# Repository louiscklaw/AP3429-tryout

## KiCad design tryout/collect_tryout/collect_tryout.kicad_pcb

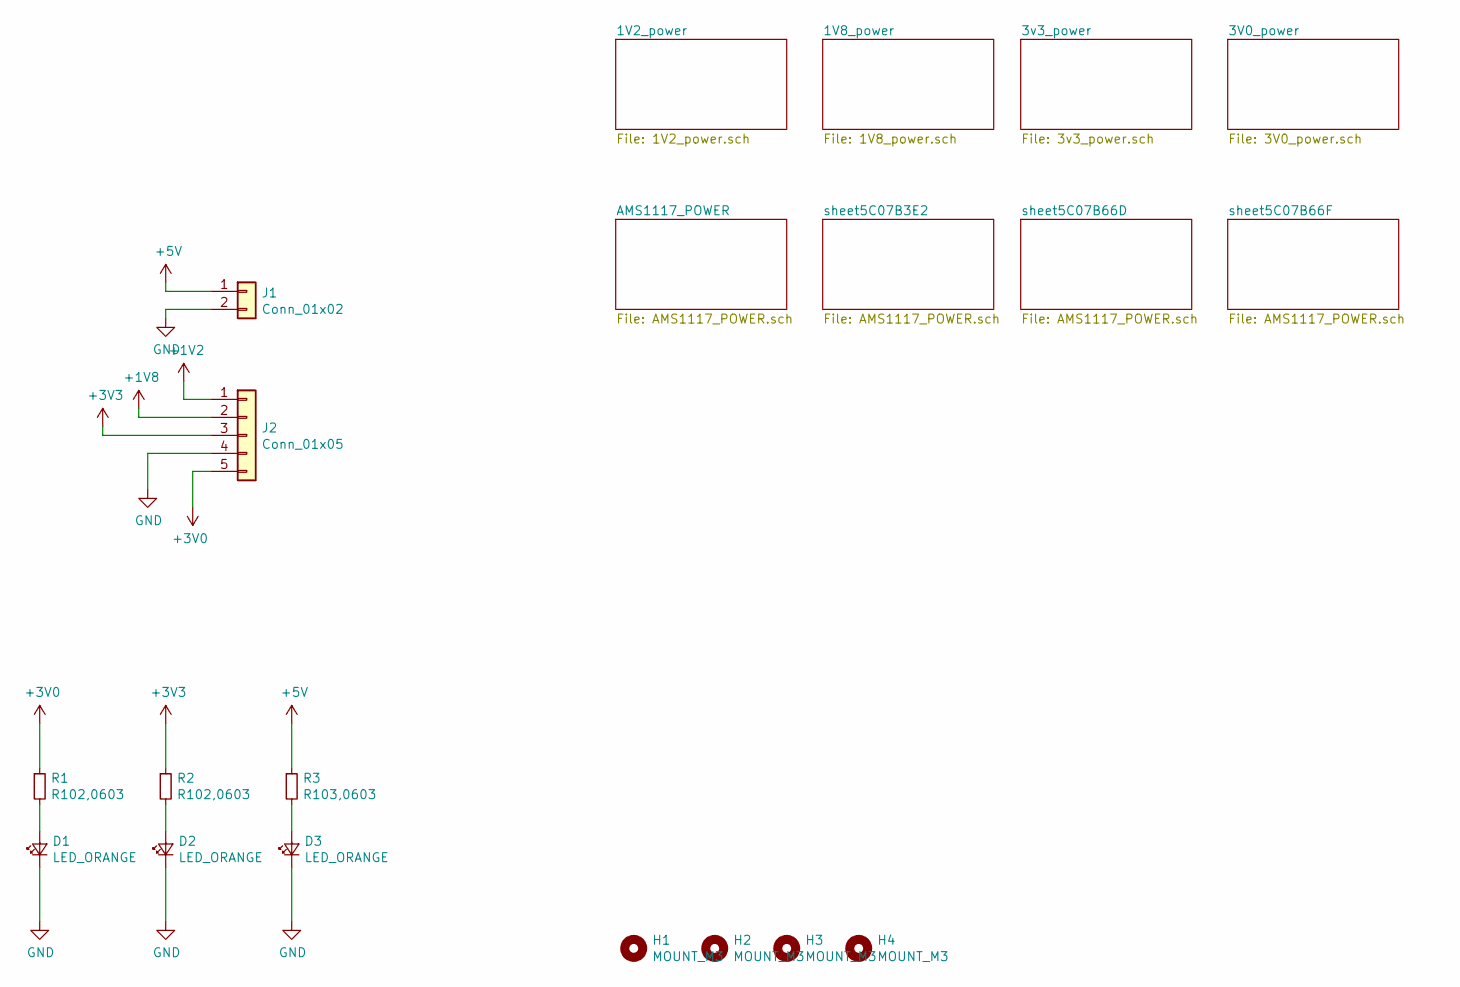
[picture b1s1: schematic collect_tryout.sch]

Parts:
D1, D2, D3: LED_ORANGE; LED_0805_2012Metric_Castellated
H1, H2, H3, H4: MOUNT_M3; MountingHole_3.2mm_M3_DIN965
J1: Conn_01x02; PinHeader_1x02_P2.54mm_Vertical
J2: Conn_01x05; PinHeader_1x05_P2.54mm_Vertical
R1, R2: R102,0603; R_0603_1608Metric_Pad1.05x0.95mm_HandSolder
R3: R103,0603; R_0603_1608Metric_Pad1.05x0.95mm_HandSolder

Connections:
+1V2: J2.1; also elsewhere on the board
+1V8: J2.2; also elsewhere on the board
+3V0: J2.5, R1.1; also elsewhere on the board
+3V3: J2.3, R2.1; also elsewhere on the board
+5V: J1.1, R3.1; also elsewhere on the board
GND: D1.1 (K), D2.1 (K), D3.1 (K), J1.2, J2.4; also elsewhere on the board
unnamed: D1.2 (A), R1.2
unnamed: D2.2 (A), R2.2
unnamed: D3.2 (A), R3.2

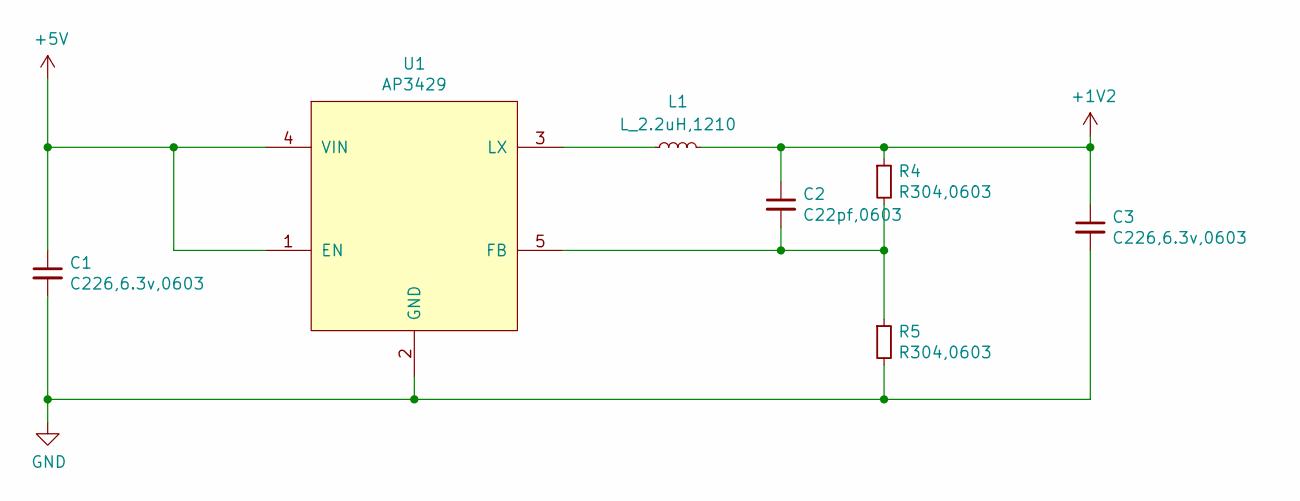
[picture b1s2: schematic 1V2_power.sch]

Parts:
C1, C3: C226,6.3v,0603; C_0603_1608Metric_Pad1.05x0.95mm_HandSolder
C2: C22pf,0603; C_0603_1608Metric_Pad1.05x0.95mm_HandSolder
L1: L_2.2uH,1210; L_1210_3225Metric_Pad1.42x2.65mm_HandSolder
R4, R5: R304,0603; R_0603_1608Metric_Pad1.05x0.95mm_HandSolder
U1: AP3429; TSOT-23-5

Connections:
+1V2: C2.1, C3.1, L1.2, R4.1; also elsewhere on the board
+5V: C1.1, U1.1 (EN), U1.4 (VIN); also elsewhere on the board
GND: C1.2, C3.2, R5.2, U1.2 (GND); also elsewhere on the board
unnamed: C2.2, R4.2, R5.1, U1.5 (FB)
unnamed: L1.1, U1.3 (LX)

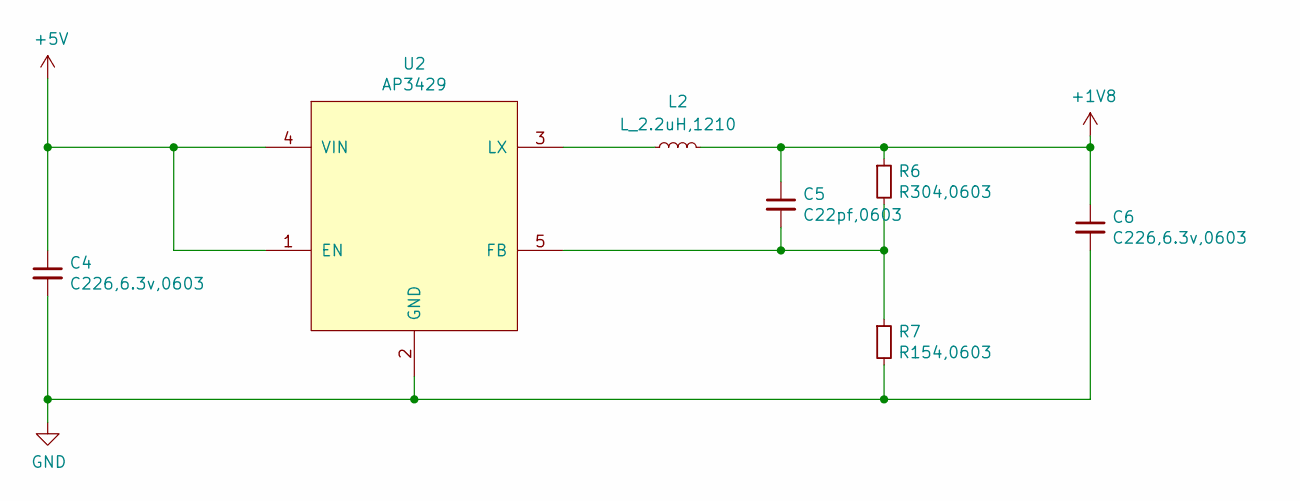
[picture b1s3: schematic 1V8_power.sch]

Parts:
C4, C6: C226,6.3v,0603; C_0603_1608Metric_Pad1.05x0.95mm_HandSolder
C5: C22pf,0603; C_0603_1608Metric_Pad1.05x0.95mm_HandSolder
L2: L_2.2uH,1210; L_1210_3225Metric_Pad1.42x2.65mm_HandSolder
R6: R304,0603; R_0603_1608Metric_Pad1.05x0.95mm_HandSolder
R7: R154,0603; R_0603_1608Metric_Pad1.05x0.95mm_HandSolder
U2: AP3429; TSOT-23-5

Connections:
+1V8: C5.1, C6.1, L2.2, R6.1; also elsewhere on the board
+5V: C4.1, U2.1 (EN), U2.4 (VIN); also elsewhere on the board
GND: C4.2, C6.2, R7.2, U2.2 (GND); also elsewhere on the board
unnamed: C5.2, R6.2, R7.1, U2.5 (FB)
unnamed: L2.1, U2.3 (LX)

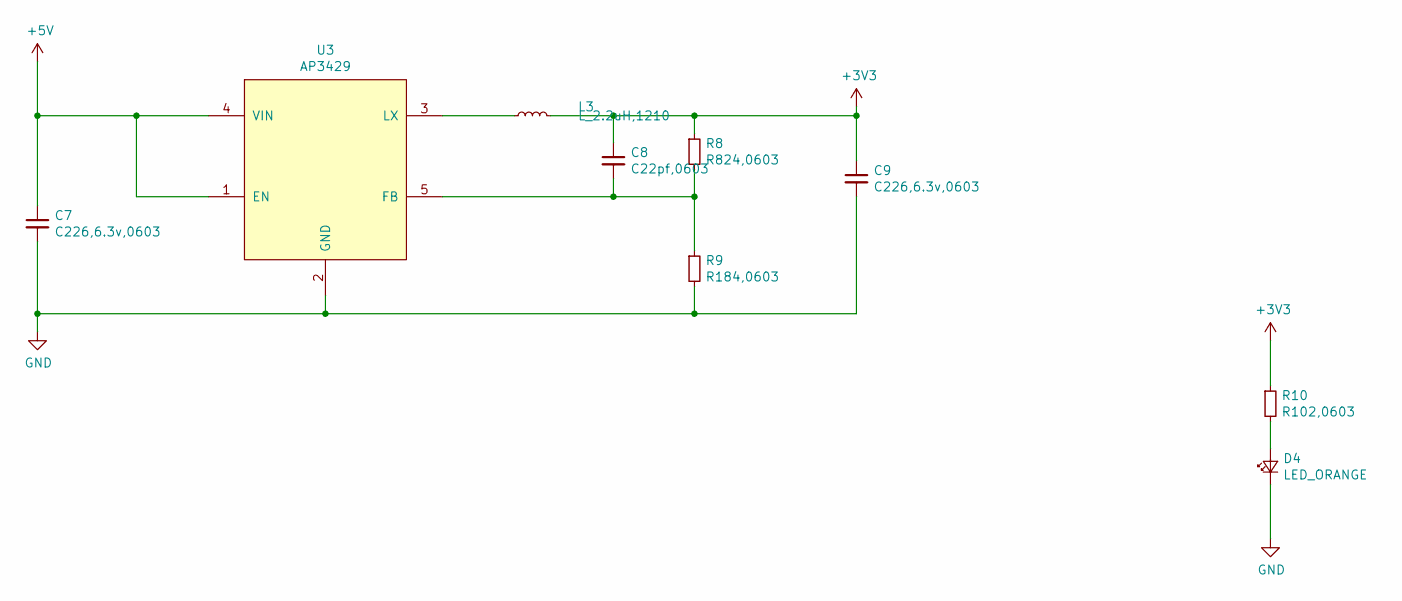
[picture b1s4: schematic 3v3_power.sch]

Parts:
C7, C9: C226,6.3v,0603; C_0603_1608Metric_Pad1.05x0.95mm_HandSolder
C8: C22pf,0603; C_0603_1608Metric_Pad1.05x0.95mm_HandSolder
D4: LED_ORANGE; LED_0805_2012Metric_Castellated
L3: L_2.2uH,1210; L_1210_3225Metric_Pad1.42x2.65mm_HandSolder
R8: R824,0603; R_0603_1608Metric_Pad1.05x0.95mm_HandSolder
R9: R184,0603; R_0603_1608Metric_Pad1.05x0.95mm_HandSolder
R10: R102,0603; R_0603_1608Metric_Pad1.05x0.95mm_HandSolder
U3: AP3429; TSOT-23-5

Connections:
+3V3: C8.1, C9.1, L3.2, R8.1, R10.1; also elsewhere on the board
+5V: C7.1, U3.1 (EN), U3.4 (VIN); also elsewhere on the board
GND: C7.2, C9.2, D4.1 (K), R9.2, U3.2 (GND); also elsewhere on the board
unnamed: C8.2, R8.2, R9.1, U3.5 (FB)
unnamed: D4.2 (A), R10.2
unnamed: L3.1, U3.3 (LX)

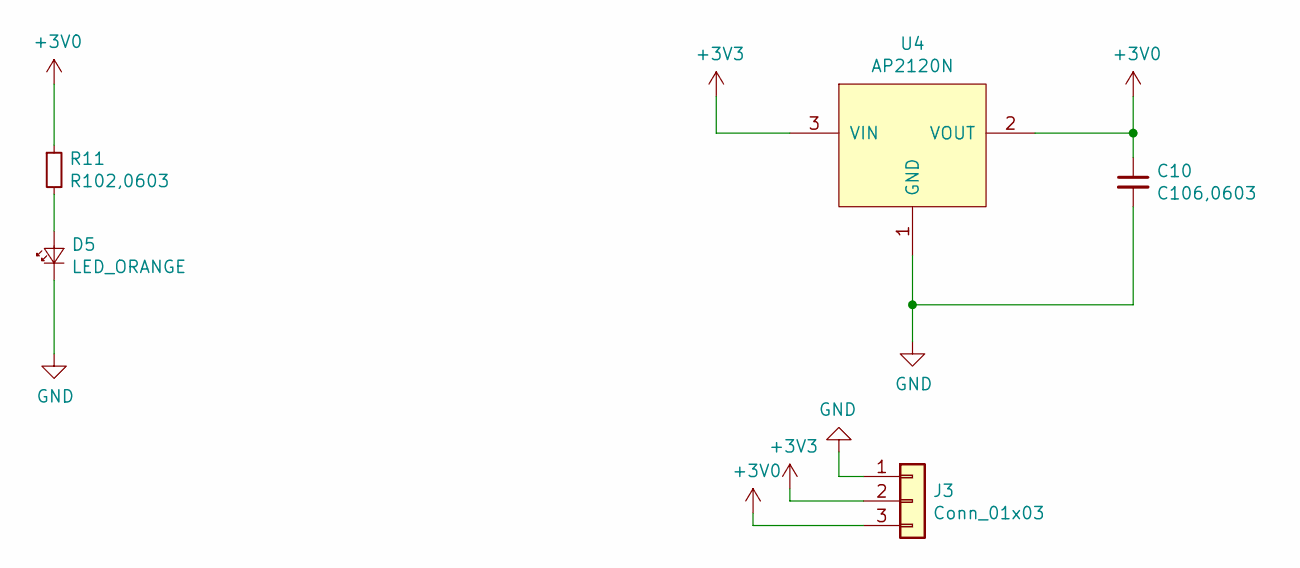
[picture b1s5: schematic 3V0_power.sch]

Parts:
C10: C106,0603; C_0603_1608Metric_Pad1.05x0.95mm_HandSolder
D5: LED_ORANGE; LED_0805_2012Metric_Castellated
J3: Conn_01x03; PinHeader_1x03_P2.54mm_Vertical
R11: R102,0603; R_0603_1608Metric_Pad1.05x0.95mm_HandSolder
U4: AP2120N; SOT-23_Handsoldering

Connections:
+3V0: C10.1, J3.3, R11.1, U4.2 (VOUT); also elsewhere on the board
+3V3: J3.2, U4.3 (VIN); also elsewhere on the board
GND: C10.2, D5.1 (K), J3.1, U4.1 (GND); also elsewhere on the board
unnamed: D5.2 (A), R11.2

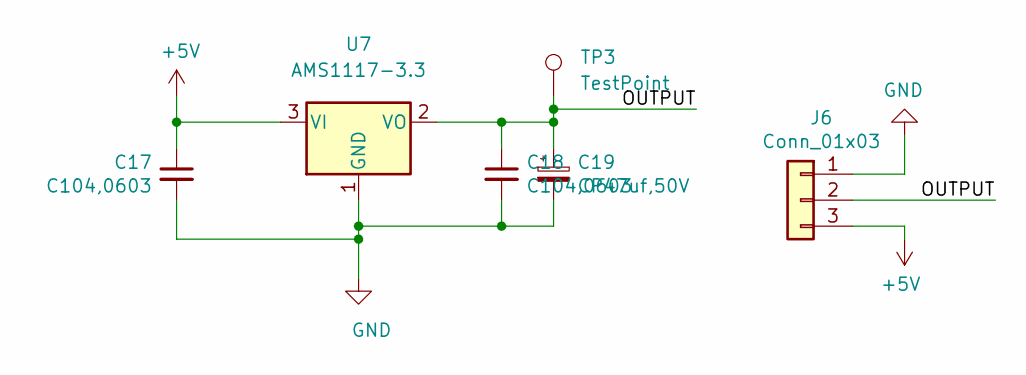
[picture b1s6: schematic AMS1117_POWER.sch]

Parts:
C11, C12: C104,0603; C_0603_1608Metric_Pad1.05x0.95mm_HandSolder
C13: CP47uf,50V; c_elec_6.3x7.7
J4: Conn_01x03; PinHeader_1x03_P2.54mm_Vertical
TP1: TestPoint; TestPoint_Keystone_5019_Minature
U5: AMS1117-3.3; SOT-223-3_TabPin2

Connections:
+5V: C11.1, J4.3, U5.3 (VI); also elsewhere on the board
/AMS1117_POWER/OUTPUT: C12.1, C13.1, J4.2, TP1.1, U5.2 (VO)
GND: C11.2, C12.2, C13.2, J4.1, U5.1 (GND); also elsewhere on the board

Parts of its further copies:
C14, C15, C17, C18, C20, C21: C104,0603; C_0603_1608Metric_Pad1.05x0.95mm_HandSolder
C16, C19, C22: CP47uf,50V; c_elec_6.3x7.7
J5, J6, J7: Conn_01x03; PinHeader_1x03_P2.54mm_Vertical
TP2, TP3, TP4: TestPoint; TestPoint_Keystone_5019_Minature
U6, U7, U8: AMS1117-3.3; SOT-223-3_TabPin2

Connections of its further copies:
+5V: C14.1, C17.1, C20.1, J5.3, J6.3, J7.3, U6.3 (VI), U7.3 (VI), U8.3 (VI); also elsewhere on the board
/sheet5C07B3E2/OUTPUT: C15.1, C16.1, J5.2, TP2.1, U6.2 (VO)
/sheet5C07B66D/OUTPUT: C18.1, C19.1, J6.2, TP3.1, U7.2 (VO)
/sheet5C07B66F/OUTPUT: C21.1, C22.1, J7.2, TP4.1, U8.2 (VO)
GND: C14.2, C15.2, C16.2, C17.2, C18.2, C19.2, C20.2, C21.2, C22.2, J5.1, J6.1, J7.1, U6.1 (GND), U7.1 (GND), U8.1 (GND); also elsewhere on the board

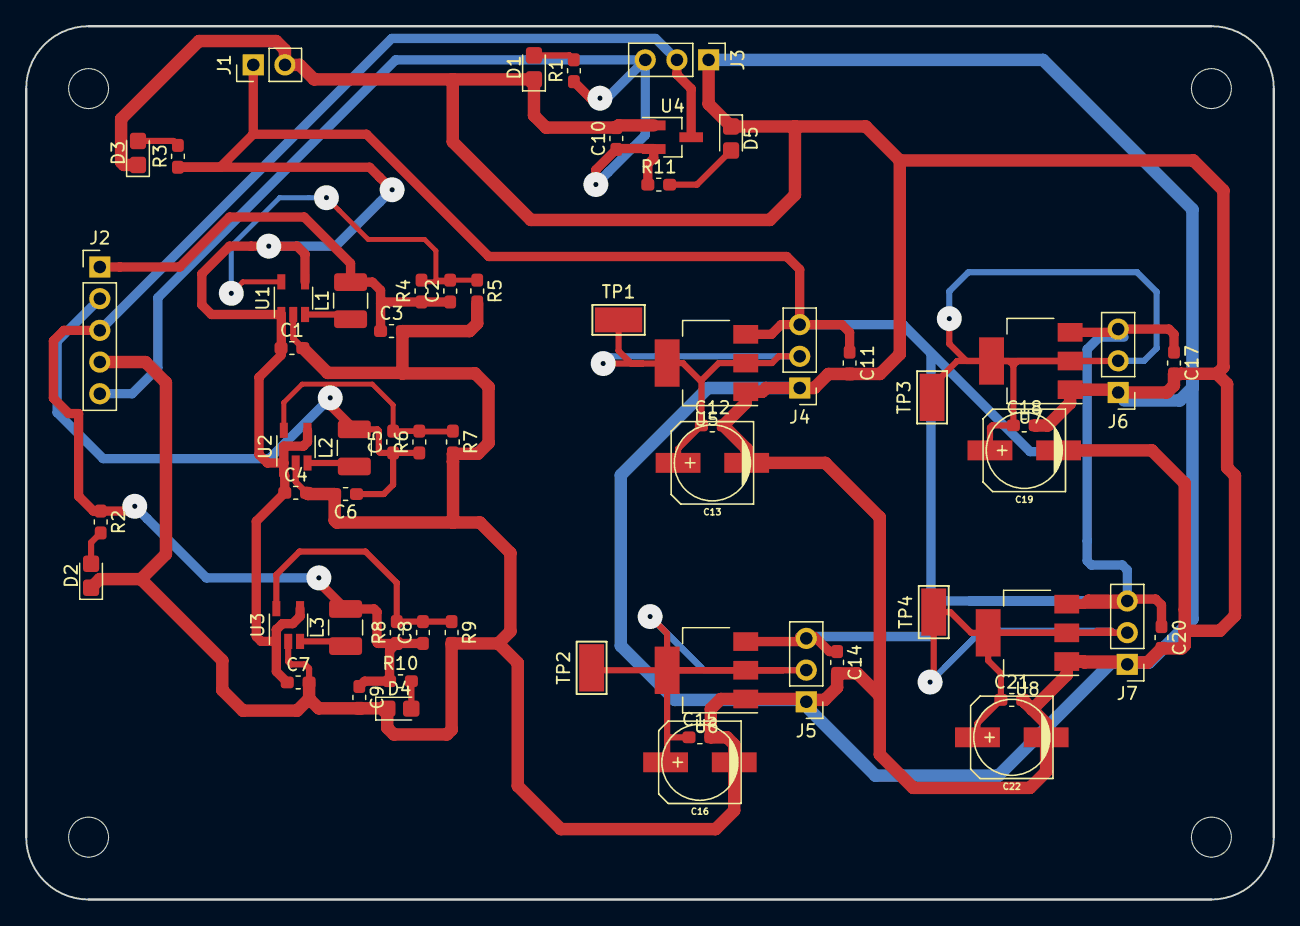
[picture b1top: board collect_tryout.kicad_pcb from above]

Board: 2 copper layers, 100.0 x 70.0 mm, 64 parts (0 on the bottom side), 21 nets.

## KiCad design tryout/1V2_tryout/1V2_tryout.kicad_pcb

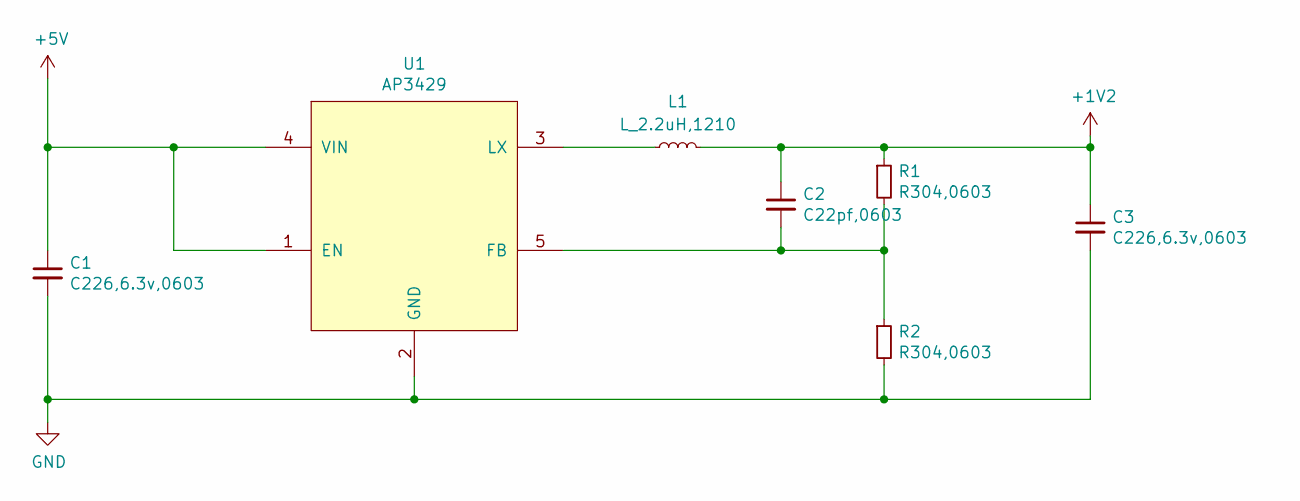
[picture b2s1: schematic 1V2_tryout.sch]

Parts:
C1, C3: C226,6.3v,0603; C_0603_1608Metric_Pad1.05x0.95mm_HandSolder
C2: C22pf,0603; C_0603_1608Metric_Pad1.05x0.95mm_HandSolder
L1: L_2.2uH,1210; L_1210_3225Metric_Pad1.42x2.65mm_HandSolder
R1, R2: R304,0603; R_0603_1608Metric_Pad1.05x0.95mm_HandSolder
U1: AP3429; TSOT-23-5

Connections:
+1V2: C2.1, C3.1, L1.2, R1.1
+5V: C1.1, U1.1 (EN), U1.4 (VIN)
GND: C1.2, C3.2, R2.2, U1.2 (GND)
unnamed: C2.2, R1.2, R2.1, U1.5 (FB)
unnamed: L1.1, U1.3 (LX)

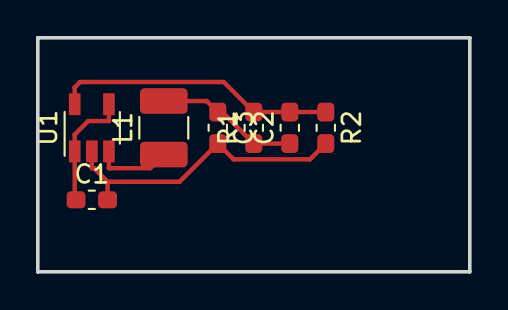
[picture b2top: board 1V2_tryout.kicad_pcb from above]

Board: 2 copper layers, 24.0 x 13.0 mm, 7 parts (0 on the bottom side), 5 nets.

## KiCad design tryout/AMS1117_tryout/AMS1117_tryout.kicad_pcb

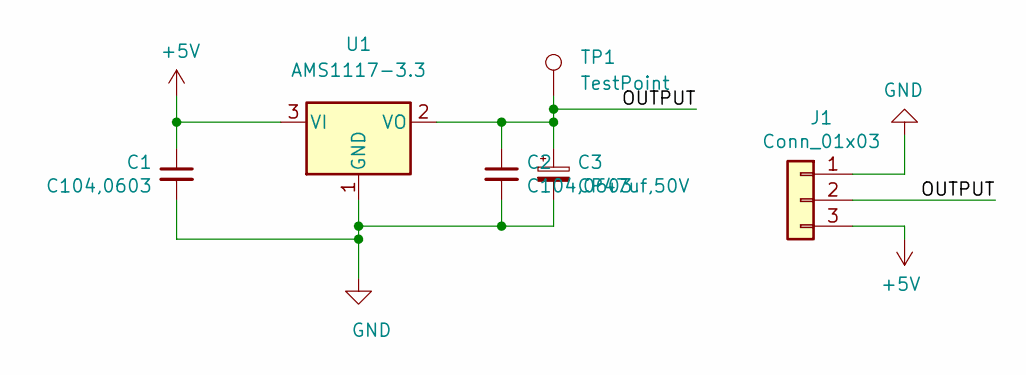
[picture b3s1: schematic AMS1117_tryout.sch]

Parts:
C1, C2: C104,0603; C_0603_1608Metric_Pad1.05x0.95mm_HandSolder
C3: CP47uf,50V; c_elec_6.3x7.7
J1: Conn_01x03; PinHeader_1x03_P2.54mm_Vertical
TP1: TestPoint; TestPoint_Keystone_5019_Minature
U1: AMS1117-3.3; SOT-223-3_TabPin2

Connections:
+5V: C1.1, J1.3, U1.3 (VI)
/OUTPUT: C2.1, C3.1, J1.2, TP1.1, U1.2 (VO)
GND: C1.2, C2.2, C3.2, J1.1, U1.1 (GND)

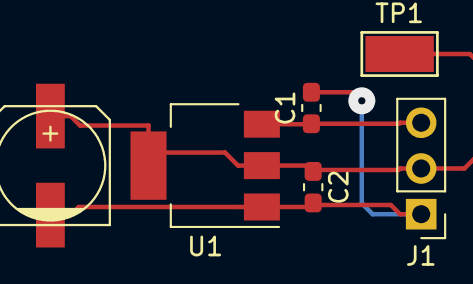
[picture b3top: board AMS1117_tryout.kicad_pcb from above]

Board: 2 copper layers, 6 parts (0 on the bottom side), 3 nets.

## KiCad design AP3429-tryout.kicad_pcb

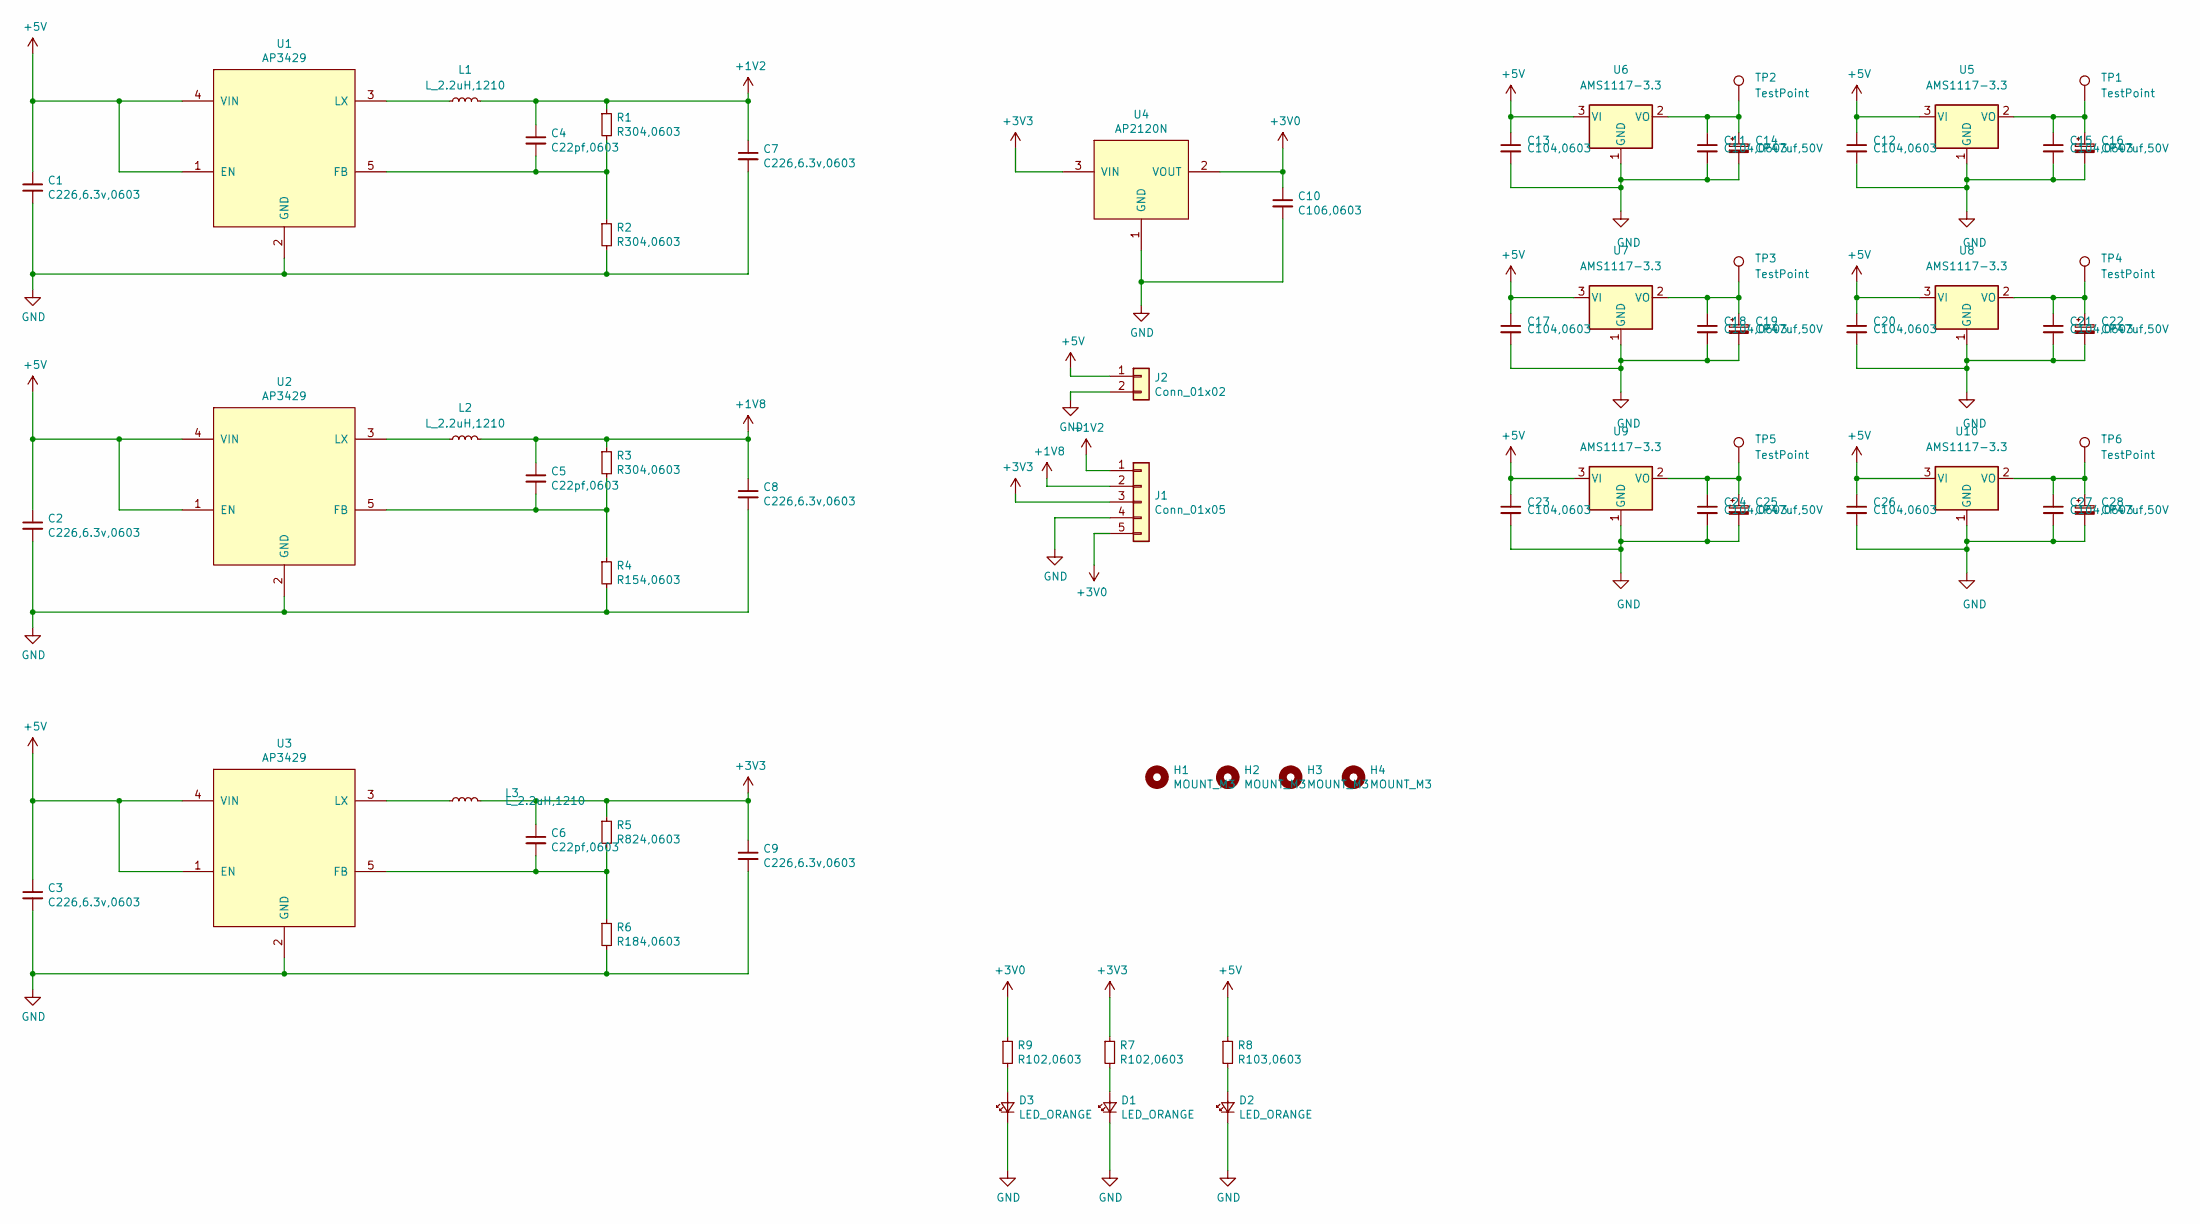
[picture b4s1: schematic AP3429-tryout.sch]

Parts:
C1, C2, C3, C7, C8, C9: C226,6.3v,0603; C_0603_1608Metric_Pad1.05x0.95mm_HandSolder
C4, C5, C6: C22pf,0603; C_0603_1608Metric_Pad1.05x0.95mm_HandSolder
C10: C106,0603; C_0603_1608Metric_Pad1.05x0.95mm_HandSolder
C11, C12, C13, C15, C17, C18, C20, C21, C23, C24, C26, C27: C104,0603; C_0603_1608Metric_Pad1.05x0.95mm_HandSolder
C14, C16, C19, C22, C25, C28: CP47uf,50V; c_elec_6.3x7.7
D1, D2, D3: LED_ORANGE; LED_0805_2012Metric_Castellated
H1, H2, H3, H4: MOUNT_M3; MountingHole_3.2mm_M3_DIN965
J1: Conn_01x05; PinHeader_1x05_P2.54mm_Vertical
J2: Conn_01x02; PinHeader_1x02_P2.54mm_Vertical
L1, L2, L3: L_2.2uH,1210; L_1210_3225Metric_Pad1.42x2.65mm_HandSolder
R1, R2, R3: R304,0603; R_0603_1608Metric_Pad1.05x0.95mm_HandSolder
R4: R154,0603; R_0603_1608Metric_Pad1.05x0.95mm_HandSolder
R5: R824,0603; R_0603_1608Metric_Pad1.05x0.95mm_HandSolder
R6: R184,0603; R_0603_1608Metric_Pad1.05x0.95mm_HandSolder
R7, R9: R102,0603; R_0603_1608Metric_Pad1.05x0.95mm_HandSolder
R8: R103,0603; R_0603_1608Metric_Pad1.05x0.95mm_HandSolder
TP1, TP2, TP3, TP4, TP5, TP6: TestPoint; TestPoint_Keystone_5019_Minature
U1, U2, U3: AP3429; TSOT-23-5
U4: AP2120N; SOT-23_Handsoldering
U5, U6, U7, U8, U9, U10: AMS1117-3.3; SOT-223-3_TabPin2

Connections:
+1V2: C4.1, C7.1, J1.1, L1.2, R1.1
+1V8: C5.1, C8.1, J1.2, L2.2, R3.1
+3V0: C10.1, J1.5, R9.1, U4.2 (VOUT)
+3V3: C6.1, C9.1, J1.3, L3.2, R5.1, R7.1, U4.3 (VIN)
+5V: C1.1, C2.1, C3.1, C12.1, C13.1, C17.1, C20.1, C23.1, C26.1, J2.1, R8.1, U1.1 (EN), U1.4 (VIN), U2.1 (EN), U2.4 (VIN), U3.1 (EN), U3.4 (VIN), U5.3 (VI), U6.3 (VI), U7.3 (VI), U8.3 (VI), U9.3 (VI), U10.3 (VI)
GND: C1.2, C2.2, C3.2, C7.2, C8.2, C9.2, C10.2, C11.2, C12.2, C13.2, C14.2, C15.2, C16.2, C17.2, C18.2, C19.2, C20.2, C21.2, C22.2, C23.2, C24.2, C25.2, C26.2, C27.2, C28.2, D1.1 (K), D2.1 (K), D3.1 (K), J1.4, J2.2, R2.2, R4.2, R6.2, U1.2 (GND), U2.2 (GND), U3.2 (GND), U4.1 (GND), U5.1 (GND), U6.1 (GND), U7.1 (GND), U8.1 (GND), U9.1 (GND), U10.1 (GND)
unnamed: C4.2, R1.2, R2.1, U1.5 (FB)
unnamed: C5.2, R3.2, R4.1, U2.5 (FB)
unnamed: C6.2, R5.2, R6.1, U3.5 (FB)
unnamed: C11.1, C14.1, TP2.1, U6.2 (VO)
unnamed: C15.1, C16.1, TP1.1, U5.2 (VO)
unnamed: C18.1, C19.1, TP3.1, U7.2 (VO)
unnamed: C21.1, C22.1, TP4.1, U8.2 (VO)
unnamed: C24.1, C25.1, TP5.1, U9.2 (VO)
unnamed: C27.1, C28.1, TP6.1, U10.2 (VO)
unnamed: D1.2 (A), R7.2
unnamed: D2.2 (A), R8.2
unnamed: D3.2 (A), R9.2
unnamed: L1.1, U1.3 (LX)
unnamed: L2.1, U2.3 (LX)
unnamed: L3.1, U3.3 (LX)

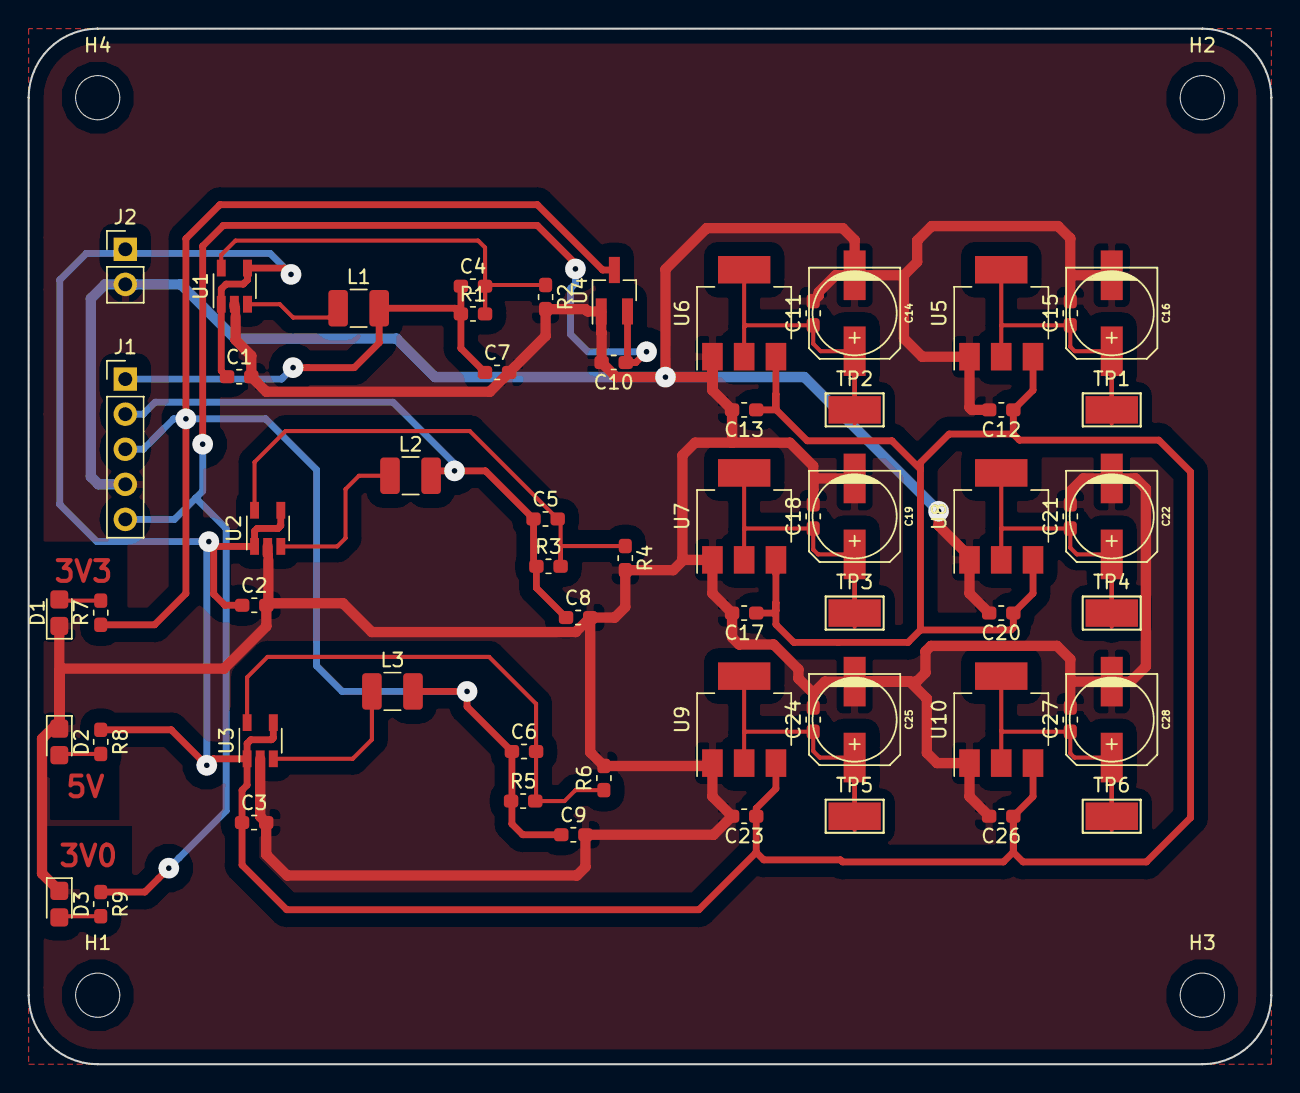
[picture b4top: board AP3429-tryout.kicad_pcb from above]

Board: 2 copper layers, 90.0 x 75.0 mm, 65 parts (0 on the bottom side), 21 nets.

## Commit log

2018-12-02 update,
2020-05-05 ci: init travis build config,
2020-05-05 ci: init travis token,
